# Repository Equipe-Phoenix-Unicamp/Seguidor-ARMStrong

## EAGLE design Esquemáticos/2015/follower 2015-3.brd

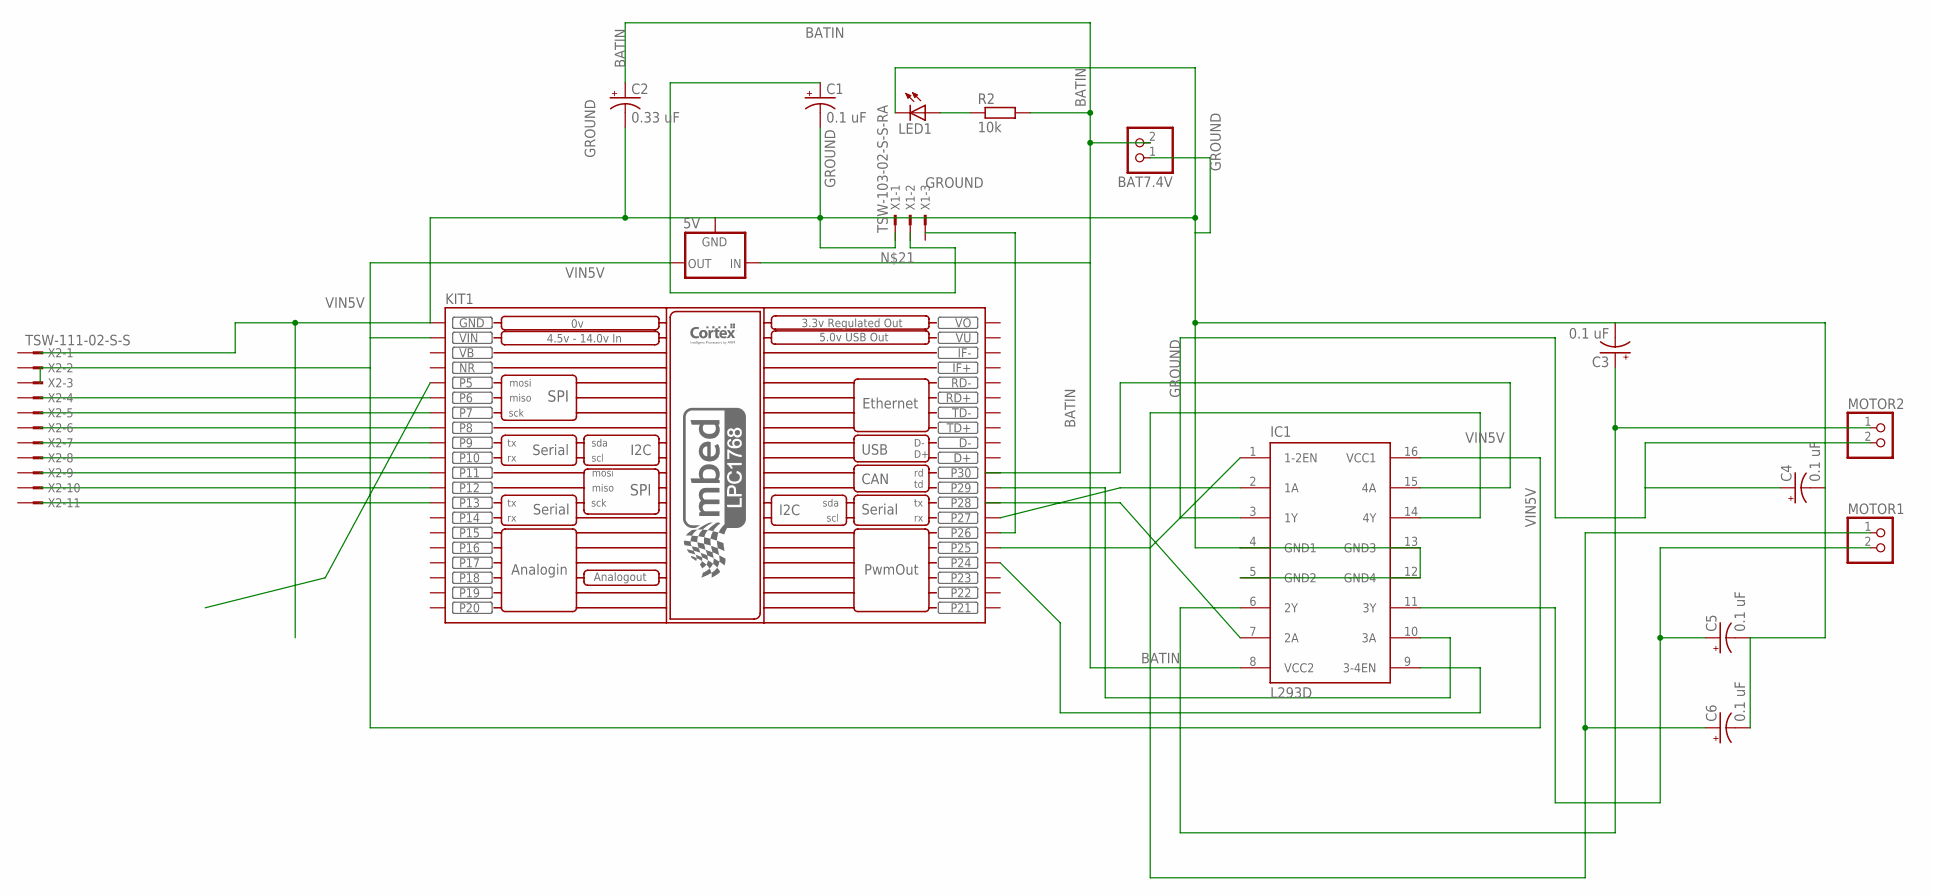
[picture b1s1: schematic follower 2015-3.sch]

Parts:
5V: 78XXL
BAT7.4V: PINHD-1X2; 1X02
C1, C3, C4, C5, C6: 0.1 uF; TT5D6
C2: 0.33 uF; TT5D6
IC1: L293D; DIL16
KIT1: MBED_NXP_LPC1768; MBED-KIT
LED1: LED3MM
MOTOR1, MOTOR2: PINHD-1X2; 1X02
R2: 10k; 0204/5
X1: TSW-103-02-S-S-RA
X2: TSW-111-02-S-S

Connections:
BATIN: BAT7.4V.2, C2.+, IC1.8 (VCC2), R2.2
GROUND: 5V.GND, BAT7.4V.1, C1.-, C2.-, C3.-, C4.-, C5.-, C6.-, IC1.4 (GND1), IC1.5 (GND2), IC1.12 (GND4), IC1.13 (GND3), KIT1.GND, LED1.K (C)
MOTOR2: C4.+, IC1.3 (1Y), MOTOR2.2
unnamed: IC1.15 (4A), KIT1.P$30 (P30)
unnamed: IC1.2 (1A), KIT1.P$27 (P27)
unnamed: IC1.1 (1-2EN), KIT1.P$25 (P25)
unnamed: IC1.10 (3A), KIT1.P$29 (P29)
unnamed: C3.+, IC1.6 (2Y), MOTOR2.1
unnamed: C5.+, IC1.11 (3Y), MOTOR1.2
unnamed: C6.+, IC1.14 (4Y), MOTOR1.1
unnamed: LED1.A, R2.1
unnamed: IC1.9 (3-4EN), KIT1.P$24 (P24)
NR: KIT1.NR
VB: KIT1.VB
VIN5V: 5V.OUT, C1.+, IC1.16 (VCC1), KIT1.VIN
VO: KIT1.VOUT (VO)
VU: KIT1.VU

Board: 2 copper layers, 16 parts (3 on the bottom side), 13 nets, no tracks yet.

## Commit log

2014-11-02 ARMStrong 2014
    Da forma que estava no PC do Rooney
2014-11-02 Mudanças Readme
    Precisamos fazer um Readme decente também.
2015-03-26 Esquemáticos 2013
    Esquemáticos feitos na placa de 2013
2015-03-26 Arquivos adicionais
    Adicionados arquivos de pistas de teste, testes do matlab e tutoriais já
    utilizados.
2015-04-03 Esquemáticos 2015 seguidor
2015-04-13 Esquemático montado, brincar com a board
